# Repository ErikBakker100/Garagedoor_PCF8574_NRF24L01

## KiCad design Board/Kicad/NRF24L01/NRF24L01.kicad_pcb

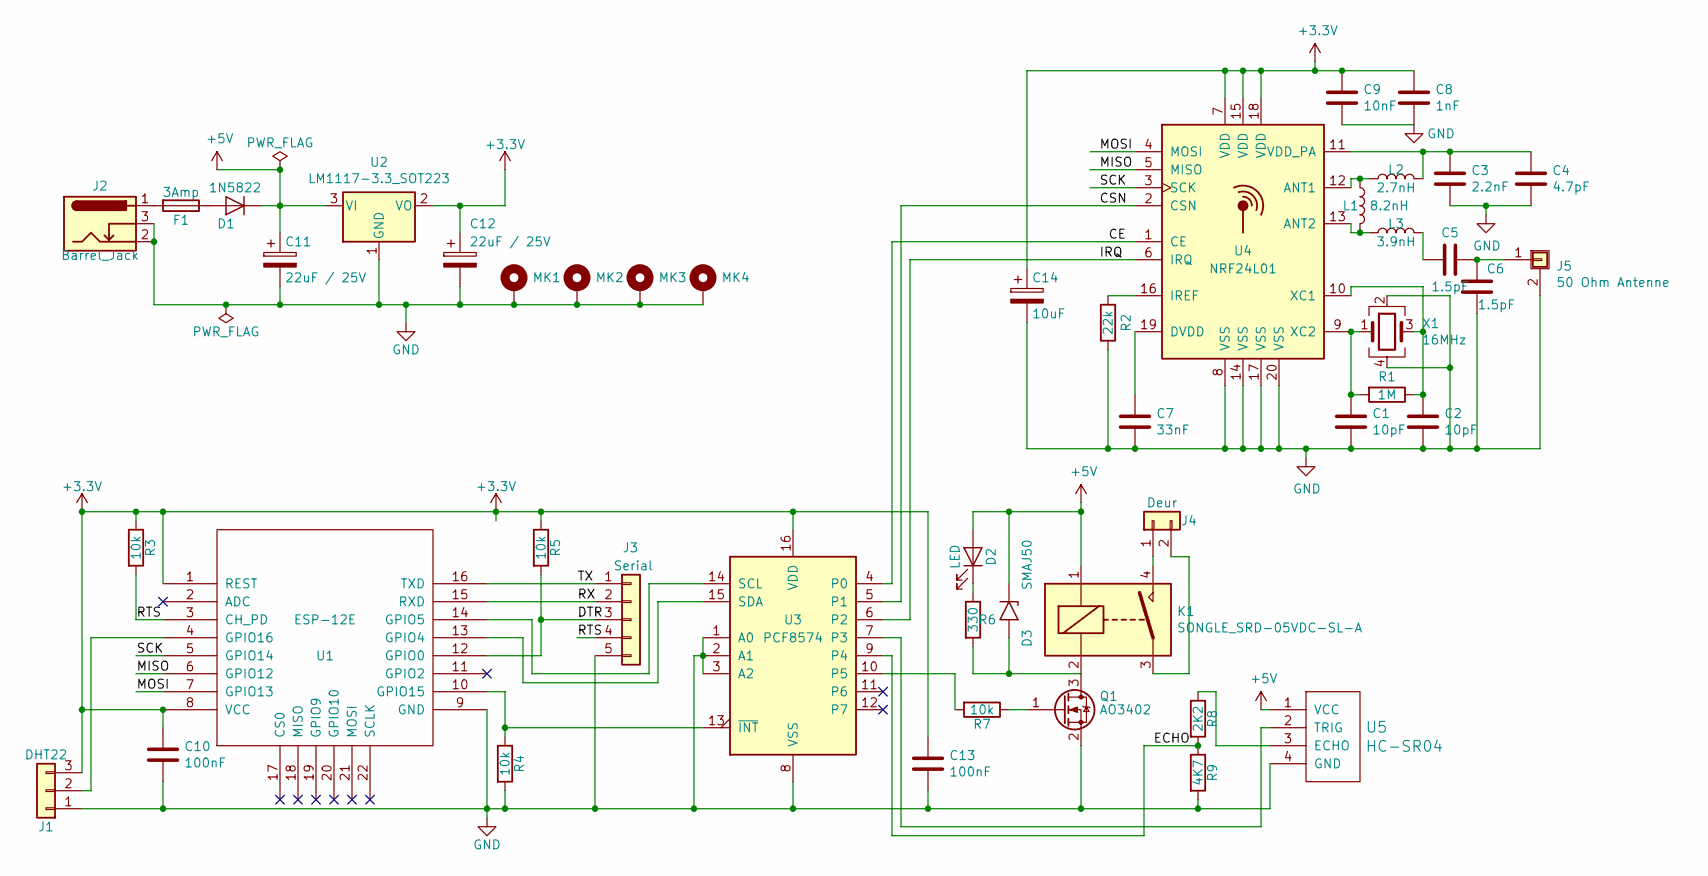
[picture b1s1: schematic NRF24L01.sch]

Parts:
C1, C2: 10pF; C_0603_1608Metric
C3: 2.2nF; C_0402_1005Metric
C4: 4.7pF; C_0402_1005Metric
C5, C6: 1.5pF; C_0402_1005Metric
C7: 33nF; C_0603_1608Metric
C8: 1nF; C_0603_1608Metric
C9: 10nF; C_0603_1608Metric
C10, C13: 100nF; C_0603_1608Metric
C11, C12: 22uF / 25V; C_1206_3216Metric
C14: 10uF; C_0603_1608Metric
D1: 1N5822; D_SMA
D2: LED; LED_0603_1608Metric
D3: SMAJ50; D_SMA
F1: 3Amp; fuse-clip-5x20mm
J1: DHT22; JST_XH_B3B-XH-AM_1x03_P2.50mm_Vertical
J2: Barrel_Jack; BarrelJack_Horizontal
J3: Serial; Molex_PicoBlade_53047-0510_1x05_P1.25mm_Vertical
J4: Deur; JST_NV_B02P-NV_1x02_P5.00mm_Vertical
J5: 50 Ohm Antenne; U.FL_Hirose_U.FL-R-SMT-1_Vertical
K1: SONGLE_SRD-05VDC-SL-A; SRD_05VDC-SL-A
L1: 8.2nH; L_0402_1005Metric
L2: 2.7nH; L_0402_1005Metric
L3: 3.9nH; L_0402_1005Metric
MK1, MK2, MK3, MK4: Mounting_Hole_PAD; MountingHole_3.2mm_M3_DIN965_Pad
Q1: AO3402; SOT-23
R1: 1M; R_0603_1608Metric
R2: 22k; R_0603_1608Metric
R3, R4, R5, R7: 10k; R_0603_1608Metric
R6: 330; R_0603_1608Metric
R8: 2K2; R_0603_1608Metric
R9: 4K7; R_0603_1608Metric
U1: ESP-12E; ESP-12E_SMD
U2: LM1117-3.3_SOT223; SOT-223-3_TabPin2
U3: PCF8574; SOIC127P1032X265-16N
U4: NRF24L01; QFN-20-1EP_4x4mm_P0.5mm_EP2.5x2.5mm
U5: HC-SR04
X1: 16MHz; Crystal_SMD_3225-4Pin_3.2x2.5mm

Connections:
+3V3: C8.1, C9.1, C10.1, C12.1, C13.1, C14.1, J1.3, R3.1, R5.1, U1.1 (REST), U1.8 (VCC), U2.2 (VO), U3.16 (VDD), U4.7 (VDD), U4.15 (VDD), U4.18 (VDD)
+5V: C11.1, D1.1 (K), D2.2 (A), D3.1 (A1), K1.1, U2.3 (VI), U5.1 (VCC)
/CE: U3.4 (P0), U4.1 (CE)
/CSN: U3.5 (P1), U4.2 (CSN)
/ECHO: R8.2, R9.1, U3.9 (P4)
/IRQ: U3.6 (P2), U4.6 (IRQ)
/MISO: U1.6 (GPIO12), U4.5 (MISO)
/MOSI: U1.7 (GPIO13), U4.4 (MOSI)
/RTS: J3.4, R3.2, U1.3 (CH_PD)
/RX: J3.2, U1.15 (RXD)
/SCK: U1.5 (GPIO14), U4.3 (SCK)
/TX: J3.1, U1.16 (TXD)
GND: C1.2, C2.2, C3.2, C4.2, C6.1, C7.2, C8.2, C9.2, C10.2, C11.2, C12.2, C13.2, C14.2, J1.1, J2.2, J2.3, J3.5, J5.2 (Shield), MK1.1, MK2.1, MK3.1, MK4.1, Q1.2 (S), R2.1, R4.2, R9.2, U1.9 (GND), U2.1 (GND), U3.1 (A0), U3.2 (A1), U3.3 (A2), U3.8 (VSS), U4.8 (VSS), U4.14 (VSS), U4.17 (VSS), U4.20 (VSS), U4.21, U5.4 (GND), X1.2, X1.4
unnamed: C1.1, R1.2, U4.9 (XC2), X1.1
unnamed: C2.1, R1.1, U4.10 (XC1), X1.3
unnamed: C3.1, C4.1, L2.2, U4.11 (VDD_PA)
unnamed: C5.1, C6.2, J5.1
unnamed: C5.2, L3.2
unnamed: C7.1, U4.19 (DVDD)
unnamed: D1.2 (A), F1.1
unnamed: D2.1 (K), R6.1
unnamed: D3.2 (A2), K1.2, Q1.3 (D), R6.2
unnamed: F1.2, J2.1
unnamed: J1.2, U1.4 (GPIO16)
unnamed: J4.1, K1.4
unnamed: J4.2, K1.3
unnamed: L1.1, L2.1, U4.12 (ANT1)
unnamed: L1.2, L3.1, U4.13 (ANT2)
unnamed: Q1.1 (G), R7.1
unnamed: R2.2, U4.16 (IREF)
unnamed: R7.2, U3.10 (P5)
unnamed: R8.1, U5.3 (ECHO)
unnamed: U1.13 (GPIO4), U3.15 (SDA)
unnamed: U1.14 (GPIO5), U3.14 (SCL)
unnamed: U3.7 (P3), U5.2 (TRIG)

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
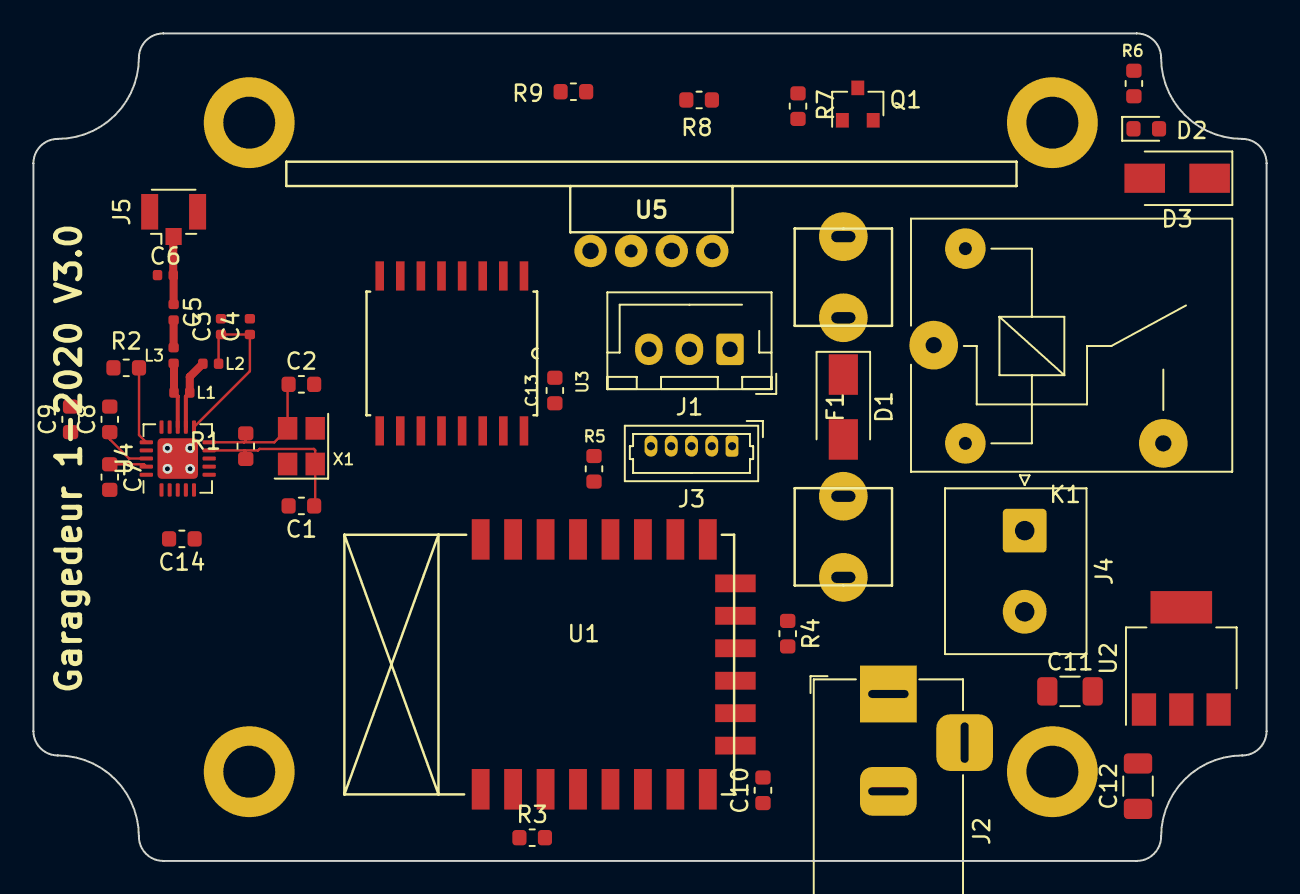
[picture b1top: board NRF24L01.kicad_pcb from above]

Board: 2 copper layers, 76.0 x 51.0 mm, 47 parts (0 on the bottom side), 37 nets.

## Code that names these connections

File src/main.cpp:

#include <Arduino.h>
#include <Wire.h>
#include <Timer.h>
#include "PCF8574.h"
#include <Ethernet.h>
#include "RF24.h"

/*
* Nodemcu board : pin number is equal to GPIO
* pin 1 = GPIO1 = TX
* pin 2 = GPIO2 = D4
* pin 3 = GPIO3 = RX
* pin 4 = GPIO4 = D2
* pin 5 = GPIO5 = D1
* pin 12 = GPIO12 = D6
* pin 13 = GPIO13 = D7
* pin 14 = GPIO14 = D5
* pin 15 = GPIO15 = D8
* pin 16 = GPIO16 = D0
*/
 
const uint8_t STATUSLEDPIN{2}; //Statusled atached to GPIO nr
const uint8_t sda{4};
const uint8_t scl{5};
const uint8_t relaisctrl{P5}; // Output to control the relais
const uint8_t nrfirq{P2}; // NRF24 IRQ input, active low and controlled by three maskable interrupt sources
const uint8_t nrfce{P0}; // active high and used to activate the chip in RX or TX mode
const uint8_t srtrig{P3}; // Trigger pin HC-SR04
const uint8_t srecho{P4}; // Echo pin HC-SR04

//#define DEBUG
#undef DEBUG

IPAddress ip(192,168,3,9);
IPAddress dns2(192,168,3,1);
IPAddress gateway(192,168,3,1); //Specify the gateway in case different from the server
IPAddress subnet(255,255,255,0);

// set in RF24_config.h #define USEPCF8574 if using PCF8574
#define CE P0 // using PCF8574 so we need to specify the pin of the PCF8574 to which the CE pin of the NRF24 is connected
#define CSN P1 // same but now for the CSN pin of the NRF24
PCF8574 PCF(0x20, sda, scl);
RF24 radio(CE, CSN);
byte addresses[][6] = {"1Node","2Node"};

// Do not modify anything below this point.
Timer t;
uint8_t SledTimerNr;
volatile bool interrupt;

ICACHE_RAM_ATTR void callback(); // to handle interrupt

void check_if_exist_I2C() {
  byte error, address;
  int nDevices;
  nDevices = 0;
  for (address = 1; address < 127; address++ )  {
    // The i2c_scanner uses the return value of
    // the Write.endTransmisstion to see if
    // a device did acknowledge to the address.
    Wire.beginTransmission(address);
    error = Wire.endTransmission();

    if (error == 0){
      Serial.print("I2C device found at address 0x");
      if (address < 16)
        Serial.print("0");
      Serial.print(address, HEX);
      Serial.println("  !");

      nDevices++;
    } else if (error == 4) {
      Serial.print("Unknow error at address 0x");
      if (address < 16)
        Serial.print("0");
      Serial.println(address, HEX);
    }
  } //for loop
  if (nDevices == 0)
    Serial.println("No I2C devices found");
}

void setup() {
  // Begin Serial on 115200
  // Remember to choose the correct Baudrate on the Serial monitor!
  Serial.begin(115200);
  Serial.print ("\r\nInitialising !\r\n");
  pinMode(15, INPUT);
  pinMode(STATUSLEDPIN, OUTPUT);
  SledTimerNr = t.oscillate(STATUSLEDPIN, 1000, HIGH);
  PCF.pinMode(nrfirq, INPUT);
  PCF.pinMode(srtrig, OUTPUT); // Trigger pin HC-SR04
  PCF.pinMode(srecho, INPUT); // Echo pin HC-SR04
  PCF.pinMode(relaisctrl, OUTPUT);
  PCF.begin();
  PCF.digitalWrite(relaisctrl, LOW);
  check_if_exist_I2C();
  SPI.beginTransaction(SPISettings(8000000, MSBFIRST, SPI_MODE0));
  radio.begin(&PCF);
  radio.setDataRate(RF24_2MBPS); //max speed
  radio.setChannel(0x4c);
  // Set the PA Level low to prevent power supply related issues since this is a
  // getting_started sketch, and the likelihood of close proximity of the devices. RF24_PA_MAX is default.
  radio.setPALevel(RF24_PA_MAX);
  // Open a writing and reading pipe on each radio, with opposite addresses
  radio.openWritingPipe(addresses[0]);
  radio.openReadingPipe(1,addresses[1]);
  // Start the radio listening for data
  radio.startListening();
  radio.printDetails();
  uint16_t tijd = millis();
  while (millis() - tijd < 500);
  attachInterrupt(digitalPinToInterrupt(15), callback, FALLING);
  wdt_disable();
}

void loop() {
  t.update(); // update all timer events;
  if (interrupt) { 
    interrupt = false;
    Serial.println("Interrupt !");
  }
  if(!PCF.isLastTransmissionSuccess()) Serial.println("Transmissie fout");
  unsigned long start_time = micros();                             // Take the time, and send it.  This will block until complete
  Serial.print(String("Sending ") + String(start_time) +"\r\n");
  boolean timeout = false;                                 // Set up a variable to indicate if a response was received or not
//  radio.stopListening();                                    // First, stop listening so we can talk. 
//  radio.write(&start_time, sizeof(unsigned long), 0);
  radio.startListening();
  unsigned long started_waiting_at = micros(); // Set up a timeout period, get the current microseconds
  while ( !radio.available()){
    // While nothing is received
    t.update();
    if (micros() - started_waiting_at > 200000 ){            // If waited longer than 200ms, indicate timeout and exit while loop
        timeout = true;
        break;
    }      
  }
  if ( timeout ){                                             // Describe the results
      Serial.print("Failed, response timed out.\r\n");
  }else{
      unsigned long got_time;                                 // Grab the response, compare, and send to debugging spew
      radio.read( &got_time, sizeof(unsigned long) );
      unsigned long end_time = micros();
      // Spew it
      Serial.print(String("Response : ") + String(got_time));
      Serial.print(String(" Round-trip delay : ") + String(end_time - start_time) + " micros\r\n");
  }
  // Try again 1s later
  unsigned long waittime{millis()};
  while (millis()-waittime < 1000) {
    t.update();
  }
  Serial.println(radio.isChipConnected()?"Ja":"Nee");
}

ICACHE_RAM_ATTR void callback() {
  interrupt = true;
}

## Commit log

2020-07-03 Start
2020-07-04 Op weg
2020-07-07 7-7-2020
2020-07-07 Board added
